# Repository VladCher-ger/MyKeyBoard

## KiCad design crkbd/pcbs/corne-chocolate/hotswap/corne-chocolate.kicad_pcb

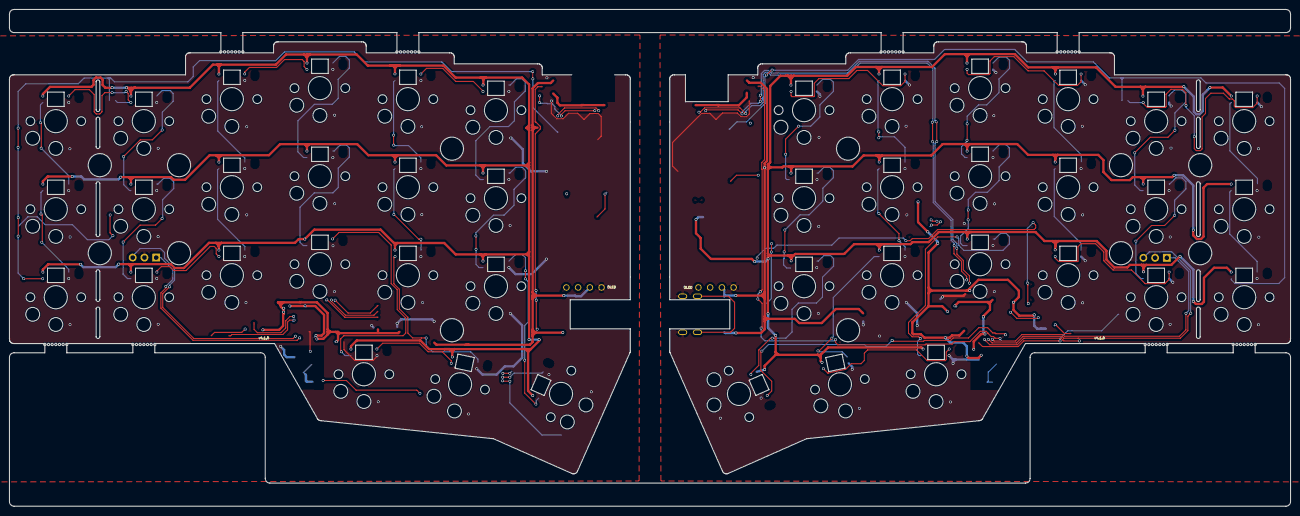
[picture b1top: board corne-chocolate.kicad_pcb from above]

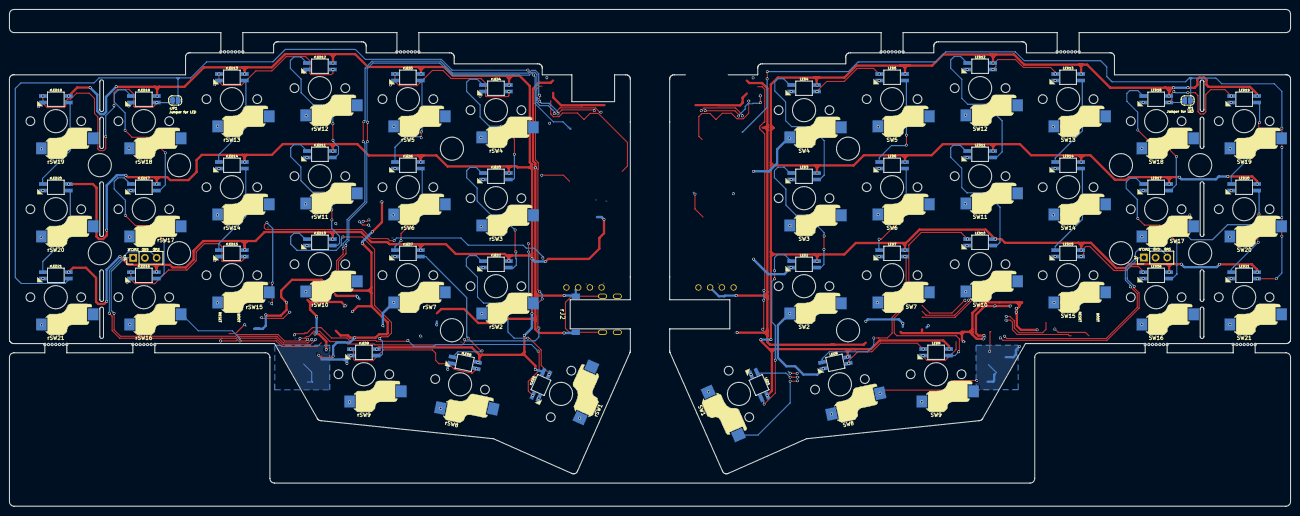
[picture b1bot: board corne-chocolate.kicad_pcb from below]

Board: 2 copper layers, 277.2 x 107.5 mm, 99 parts (89 on the bottom side), 47 nets.

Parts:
BT1, BT2, BT3, BT4: Breakaway Tabs; Breakaway_Tabs
J3: Conn_01x04; OLED
J4: Conn_01x03; PinHeader_1x03_P2.54mm_Vertical
JP1: SolderJumper_2_Bridged; SolderJumper-2_P1.3mm_Open_RoundedPad1.0x1.5mm
LED1, LED2, LED3, LED4, LED5, LED6, LED7, LED8, LED9, LED10, LED11, LED12, LED13, LED14, LED15, LED16, LED17, LED18, LED19, LED20, LED21: YS-SK6812MINI-E
SW1: SW_Push; keyswitch_choc12_hotswap_1.5u
SW2, SW3, SW4, SW5, SW6, SW7, SW8, SW9, SW10, SW11, SW12, SW13, SW14, SW15, SW16, SW17, SW18, SW19, SW20, SW21: SW_Push; keyswitch_choc12_hotswap_1u
rBT1, rBT2, rBT3, rBT4: Breakaway Tabs; Breakaway_Tabs
rJ2: TRS; PJ-398A-5A_PJ-399B-6A
rJ3: Conn_01x04; OLED
rJ4: Conn_01x03; PinHeader_1x03_P2.54mm_Vertical
rJP1: SolderJumper_2_Bridged; SolderJumper-2_P1.3mm_Open_RoundedPad1.0x1.5mm
rLED1, rLED2, rLED3, rLED4, rLED5, rLED6, rLED7, rLED8, rLED9, rLED10, rLED11, rLED12, rLED13, rLED14, rLED15, rLED16, rLED17, rLED18, rLED19, rLED20, rLED21: YS-SK6812MINI-E
rSW1: SW_Push; keyswitch_choc12_hotswap_1.5u
rSW2, rSW3, rSW4, rSW5, rSW6, rSW7, rSW8, rSW9, rSW10, rSW11, rSW12, rSW13, rSW14, rSW15, rSW16, rSW17, rSW18, rSW19, rSW20, rSW21: SW_Push; keyswitch_choc12_hotswap_1u

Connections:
+5VR: rJ2.T, rJ3.3
GND: J3.4, J4.2, LED1.3 (VSS), LED2.3 (VSS), LED3.3 (VSS), LED4.3 (VSS), LED5.3 (VSS), LED6.3 (VSS), LED7.3 (VSS), LED8.3 (VSS), LED9.3 (VSS), LED10.3 (VSS), LED11.3 (VSS), LED12.3 (VSS), LED13.3 (VSS), LED14.3 (VSS), LED15.3 (VSS), LED16.3 (VSS), LED17.3 (VSS), LED18.3 (VSS), LED19.3 (VSS), LED20.3 (VSS), LED21.3 (VSS)
GNDR: rJ2.S, rJ3.4, rJ4.2, rLED1.3 (VSS), rLED2.3 (VSS), rLED3.3 (VSS), rLED4.3 (VSS), rLED5.3 (VSS), rLED6.3 (VSS), rLED7.3 (VSS), rLED8.3 (VSS), rLED9.3 (VSS), rLED10.3 (VSS), rLED11.3 (VSS), rLED12.3 (VSS), rLED13.3 (VSS), rLED14.3 (VSS), rLED15.3 (VSS), rLED16.3 (VSS), rLED17.3 (VSS), rLED18.3 (VSS), rLED19.3 (VSS), rLED20.3 (VSS), rLED21.3 (VSS)
unnamed: JP1.1 (A), LED18.2 (DOUT), LED19.4 (DIN)
unnamed: JP1.2 (B), LED21.2 (DOUT)
unnamed: LED1.2 (DOUT), LED2.4 (DIN)
unnamed: LED1.1 (VDD), LED2.1 (VDD), LED3.1 (VDD), LED4.1 (VDD), LED5.1 (VDD), LED6.1 (VDD), LED7.1 (VDD), LED8.1 (VDD), LED9.1 (VDD), LED10.1 (VDD), LED11.1 (VDD), LED12.1 (VDD), LED13.1 (VDD), LED14.1 (VDD), LED15.1 (VDD), LED16.1 (VDD), LED17.1 (VDD), LED18.1 (VDD), LED19.1 (VDD), LED20.1 (VDD), LED21.1 (VDD)
unnamed: LED2.2 (DOUT), LED3.4 (DIN)
unnamed: LED3.2 (DOUT), LED4.4 (DIN)
unnamed: LED4.2 (DOUT), LED5.4 (DIN)
unnamed: LED5.2 (DOUT), LED6.4 (DIN)
unnamed: LED6.2 (DOUT), LED7.4 (DIN)
unnamed: LED7.2 (DOUT), LED8.4 (DIN)
unnamed: LED8.2 (DOUT), LED9.4 (DIN)
unnamed: LED9.2 (DOUT), LED10.4 (DIN)
unnamed: LED10.2 (DOUT), LED11.4 (DIN)
unnamed: LED11.2 (DOUT), LED12.4 (DIN)
unnamed: LED12.2 (DOUT), LED13.4 (DIN)
unnamed: LED13.2 (DOUT), LED14.4 (DIN)
unnamed: LED14.2 (DOUT), LED15.4 (DIN)
unnamed: LED15.2 (DOUT), LED16.4 (DIN)
unnamed: LED16.2 (DOUT), LED17.4 (DIN)
unnamed: LED17.2 (DOUT), LED18.4 (DIN)
unnamed: LED19.2 (DOUT), LED20.4 (DIN)
unnamed: LED20.2 (DOUT), LED21.4 (DIN)
unnamed: rJP1.1 (A), rLED18.2 (DOUT), rLED19.4 (DIN)
unnamed: rJP1.2 (B), rLED21.2 (DOUT)
unnamed: rLED1.2 (DOUT), rLED2.4 (DIN)
unnamed: rLED1.1 (VDD), rLED2.1 (VDD), rLED3.1 (VDD), rLED4.1 (VDD), rLED5.1 (VDD), rLED6.1 (VDD), rLED7.1 (VDD), rLED8.1 (VDD), rLED9.1 (VDD), rLED10.1 (VDD), rLED11.1 (VDD), rLED12.1 (VDD), rLED13.1 (VDD), rLED14.1 (VDD), rLED15.1 (VDD), rLED16.1 (VDD), rLED17.1 (VDD), rLED18.1 (VDD), rLED19.1 (VDD), rLED20.1 (VDD), rLED21.1 (VDD)
unnamed: rLED2.2 (DOUT), rLED3.4 (DIN)
unnamed: rLED3.2 (DOUT), rLED4.4 (DIN)
unnamed: rLED4.2 (DOUT), rLED5.4 (DIN)
unnamed: rLED5.2 (DOUT), rLED6.4 (DIN)
unnamed: rLED6.2 (DOUT), rLED7.4 (DIN)
unnamed: rLED7.2 (DOUT), rLED8.4 (DIN)
unnamed: rLED8.2 (DOUT), rLED9.4 (DIN)
unnamed: rLED9.2 (DOUT), rLED10.4 (DIN)
unnamed: rLED10.2 (DOUT), rLED11.4 (DIN)
unnamed: rLED11.2 (DOUT), rLED12.4 (DIN)
unnamed: rLED12.2 (DOUT), rLED13.4 (DIN)
unnamed: rLED13.2 (DOUT), rLED14.4 (DIN)
unnamed: rLED14.2 (DOUT), rLED15.4 (DIN)
unnamed: rLED15.2 (DOUT), rLED16.4 (DIN)
unnamed: rLED16.2 (DOUT), rLED17.4 (DIN)
unnamed: rLED17.2 (DOUT), rLED18.4 (DIN)
unnamed: rLED19.2 (DOUT), rLED20.4 (DIN)
unnamed: rLED20.2 (DOUT), rLED21.4 (DIN)

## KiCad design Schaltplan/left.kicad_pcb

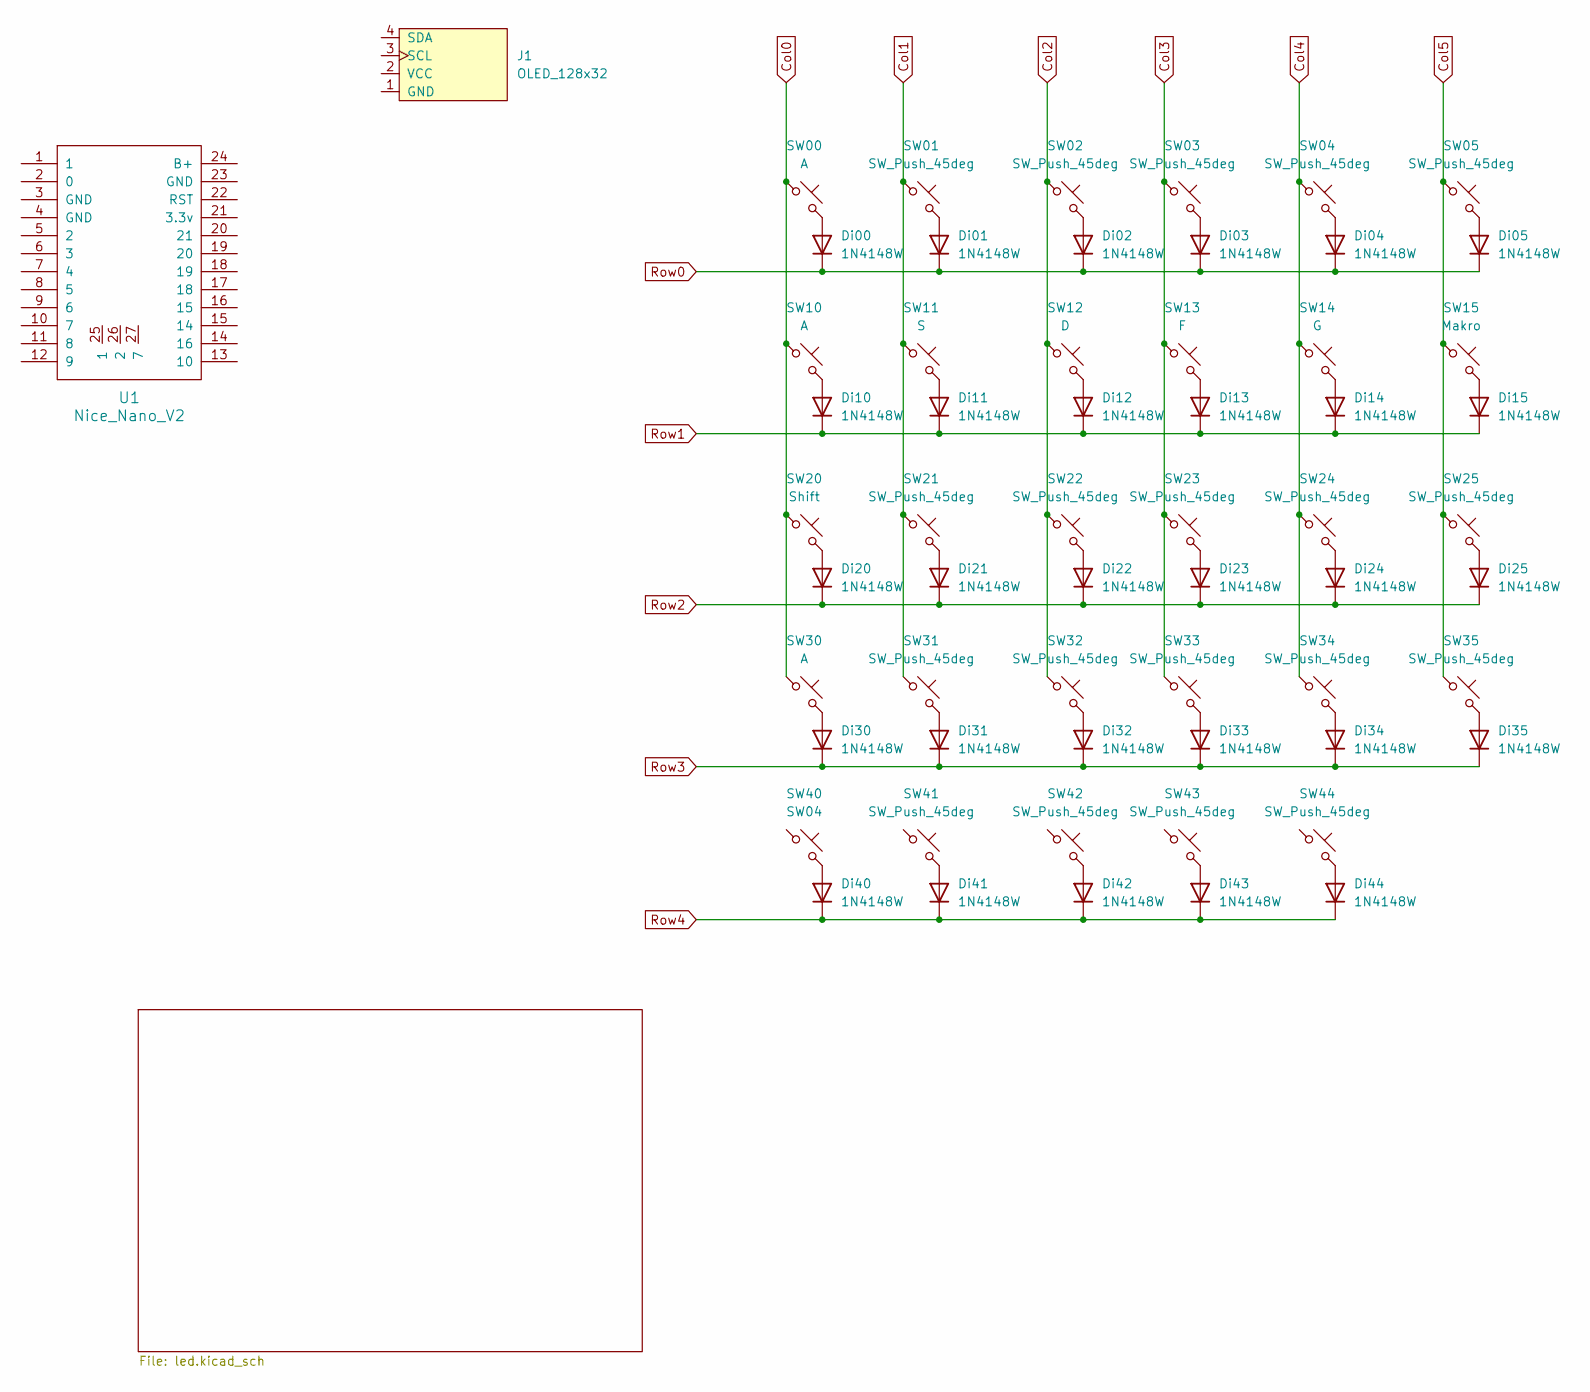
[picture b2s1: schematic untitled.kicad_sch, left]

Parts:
Di00, Di01, Di02, Di03, Di04, Di05, Di10, Di11, Di12, Di13, Di14, Di15, Di20, Di21, Di22, Di23, Di24, Di25, Di30, Di31, Di32, Di33, Di34, Di35, Di40, Di41, Di42, Di43, Di44: 1N4148W; D_SOD-123
J1: OLED_128x32
SW00, SW10, SW30: A; Hotswap_MX_1.00u
SW01, SW02, SW03, SW04, SW05, SW21, SW22, SW23, SW24, SW25, SW31, SW32, SW33, SW34, SW35, SW41, SW43, SW44: SW_Push_45deg; Hotswap_MX_1.00u
SW11: S; Hotswap_MX_1.00u
SW12: D; Hotswap_MX_1.00u
SW13: F; Hotswap_MX_1.00u
SW14: G; Hotswap_MX_1.00u
SW15: Makro; Hotswap_MX_1.00u
SW20: Shift; Hotswap_MX_1.00u
SW40: SW04; Hotswap_MX_1.00u
SW42: SW_Push_45deg; Hotswap_MX_1.75u
U1: Nice_Nano_V2

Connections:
Col0: SW00.1, SW10.1, SW20.1, SW30.1
Col1: SW01.1, SW11.1, SW21.1, SW31.1
Col2: SW02.1, SW12.1, SW22.1, SW32.1
Col3: SW03.1, SW13.1, SW23.1, SW33.1
Col4: SW04.1, SW14.1, SW24.1, SW34.1
Col5: SW05.1, SW15.1, SW25.1, SW35.1
unnamed: Di00.2 (A), SW00.2
unnamed: Di01.2 (A), SW01.2
unnamed: Di02.2 (A), SW02.2
unnamed: Di03.2 (A), SW03.2
unnamed: Di04.2 (A), SW04.2
unnamed: Di05.2 (A), SW05.2
unnamed: Di10.2 (A), SW10.2
unnamed: Di11.2 (A), SW11.2
unnamed: Di12.2 (A), SW12.2
unnamed: Di13.2 (A), SW13.2
unnamed: Di14.2 (A), SW14.2
unnamed: Di15.2 (A), SW15.2
unnamed: Di20.2 (A), SW20.2
unnamed: Di21.2 (A), SW21.2
unnamed: Di22.2 (A), SW22.2
unnamed: Di23.2 (A), SW23.2
unnamed: Di24.2 (A), SW24.2
unnamed: Di25.2 (A), SW25.2
unnamed: Di30.2 (A), SW30.2
unnamed: Di31.2 (A), SW31.2
unnamed: Di32.2 (A), SW32.2
unnamed: Di33.2 (A), SW33.2
unnamed: Di34.2 (A), SW34.2
unnamed: Di35.2 (A), SW35.2
unnamed: Di40.2 (A), SW40.2
unnamed: Di41.2 (A), SW41.2
unnamed: Di42.2 (A), SW42.2
unnamed: Di43.2 (A), SW43.2
unnamed: Di44.2 (A), SW44.2
Row0: Di00.1 (K), Di01.1 (K), Di02.1 (K), Di03.1 (K), Di04.1 (K), Di05.1 (K)
Row1: Di10.1 (K), Di11.1 (K), Di12.1 (K), Di13.1 (K), Di14.1 (K), Di15.1 (K)
Row2: Di20.1 (K), Di21.1 (K), Di22.1 (K), Di23.1 (K), Di24.1 (K), Di25.1 (K)
Row3: Di30.1 (K), Di31.1 (K), Di32.1 (K), Di33.1 (K), Di34.1 (K), Di35.1 (K)
Row4: Di40.1 (K), Di41.1 (K), Di42.1 (K), Di43.1 (K), Di44.1 (K)

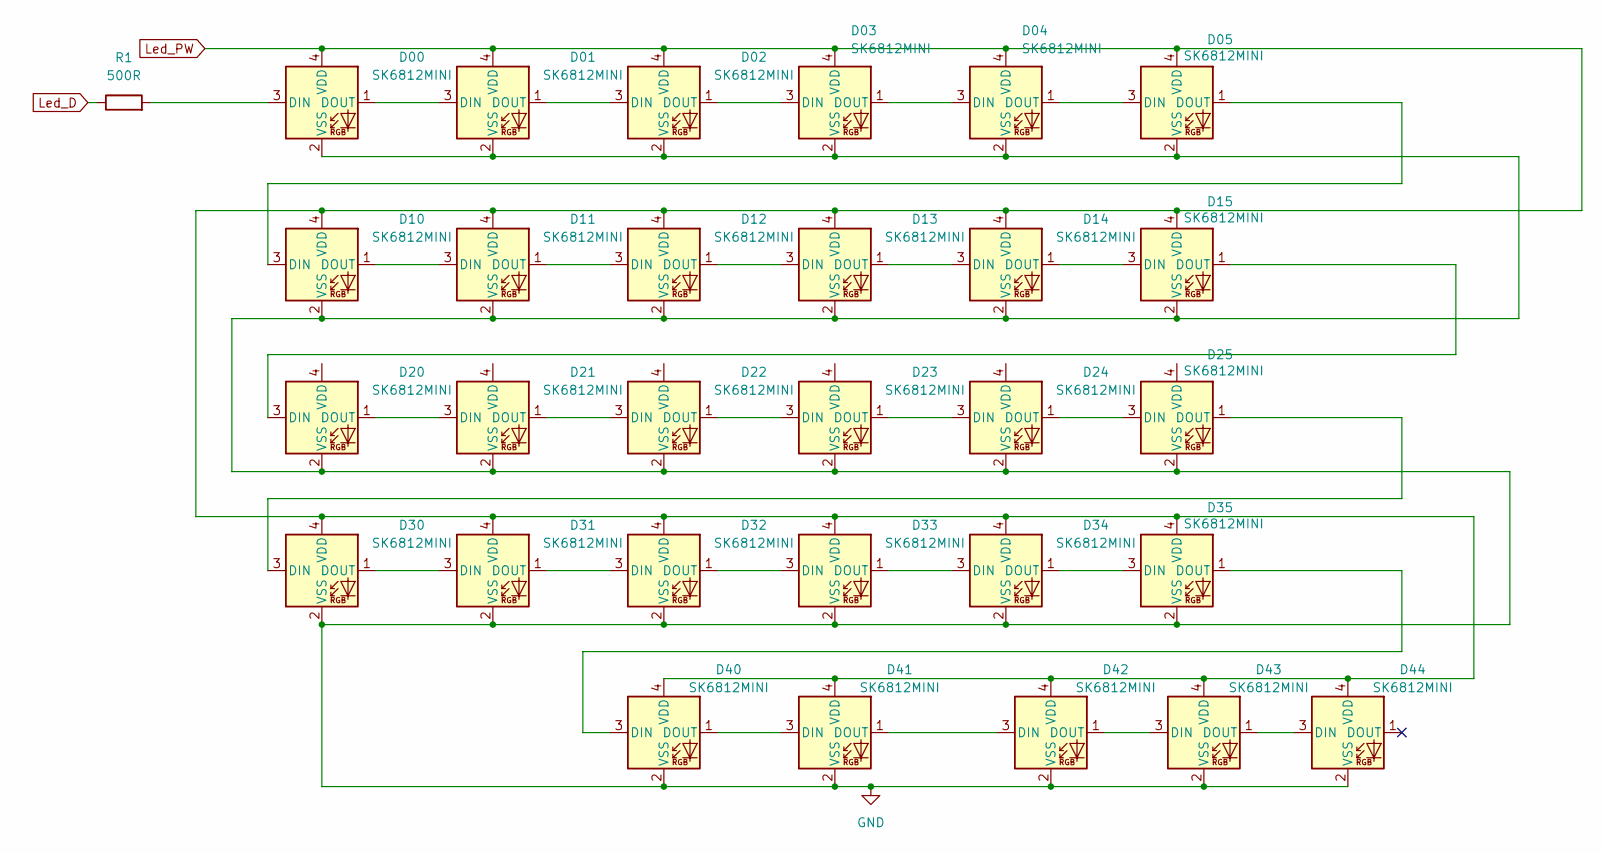
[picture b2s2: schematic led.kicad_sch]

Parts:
D00, D01, D02, D03, D04, D05, D10, D11, D12, D13, D14, D15, D20, D21, D22, D23, D24, D25, D30, D31, D32, D33, D34, D35, D40, D41, D42, D43, D44: SK6812MINI; SK6812-MINI-E
R1: 500R; R_Axial_DIN0414_L11.9mm_D4.5mm_P15.24mm_Horizontal

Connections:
GND: D00.2 (VSS), D01.2 (VSS), D02.2 (VSS), D03.2 (VSS), D04.2 (VSS), D05.2 (VSS), D10.2 (VSS), D11.2 (VSS), D12.2 (VSS), D13.2 (VSS), D14.2 (VSS), D15.2 (VSS), D20.2 (VSS), D21.2 (VSS), D22.2 (VSS), D23.2 (VSS), D24.2 (VSS), D25.2 (VSS), D30.2 (VSS), D31.2 (VSS), D32.2 (VSS), D33.2 (VSS), D34.2 (VSS), D35.2 (VSS), D40.2 (VSS), D41.2 (VSS), D42.2 (VSS), D43.2 (VSS), D44.2 (VSS)
Led_D: R1.1
Led_PW: D00.4 (VDD), D01.4 (VDD), D02.4 (VDD), D03.4 (VDD), D04.4 (VDD), D05.4 (VDD), D10.4 (VDD), D11.4 (VDD), D12.4 (VDD), D13.4 (VDD), D14.4 (VDD), D15.4 (VDD), D30.4 (VDD), D31.4 (VDD), D32.4 (VDD), D33.4 (VDD), D34.4 (VDD), D35.4 (VDD), D40.4 (VDD), D41.4 (VDD), D42.4 (VDD), D43.4 (VDD), D44.4 (VDD)
unnamed: D00.3 (DIN), R1.2
unnamed: D00.1 (DOUT), D01.3 (DIN)
unnamed: D01.1 (DOUT), D02.3 (DIN)
unnamed: D02.1 (DOUT), D03.3 (DIN)
unnamed: D03.1 (DOUT), D04.3 (DIN)
unnamed: D04.1 (DOUT), D05.3 (DIN)
unnamed: D05.1 (DOUT), D10.3 (DIN)
unnamed: D10.1 (DOUT), D11.3 (DIN)
unnamed: D11.1 (DOUT), D12.3 (DIN)
unnamed: D12.1 (DOUT), D13.3 (DIN)
unnamed: D13.1 (DOUT), D14.3 (DIN)
unnamed: D14.1 (DOUT), D15.3 (DIN)
unnamed: D15.1 (DOUT), D20.3 (DIN)
unnamed: D20.1 (DOUT), D21.3 (DIN)
unnamed: D21.1 (DOUT), D22.3 (DIN)
unnamed: D22.1 (DOUT), D23.3 (DIN)
unnamed: D23.1 (DOUT), D24.3 (DIN)
unnamed: D24.1 (DOUT), D25.3 (DIN)
unnamed: D25.1 (DOUT), D30.3 (DIN)
unnamed: D30.1 (DOUT), D31.3 (DIN)
unnamed: D31.1 (DOUT), D32.3 (DIN)
unnamed: D32.1 (DOUT), D33.3 (DIN)
unnamed: D33.1 (DOUT), D34.3 (DIN)
unnamed: D34.1 (DOUT), D35.3 (DIN)
unnamed: D35.1 (DOUT), D40.3 (DIN)
unnamed: D40.1 (DOUT), D41.3 (DIN)
unnamed: D41.1 (DOUT), D42.3 (DIN)
unnamed: D42.1 (DOUT), D43.3 (DIN)
unnamed: D43.1 (DOUT), D44.3 (DIN)

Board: 2 copper layers, 90 parts (60 on the bottom side), 71 nets, no tracks yet.

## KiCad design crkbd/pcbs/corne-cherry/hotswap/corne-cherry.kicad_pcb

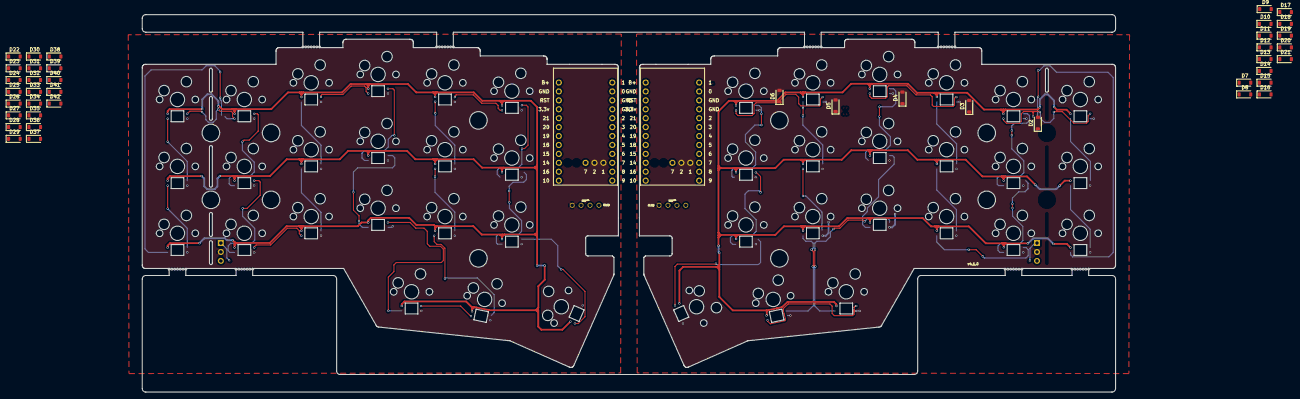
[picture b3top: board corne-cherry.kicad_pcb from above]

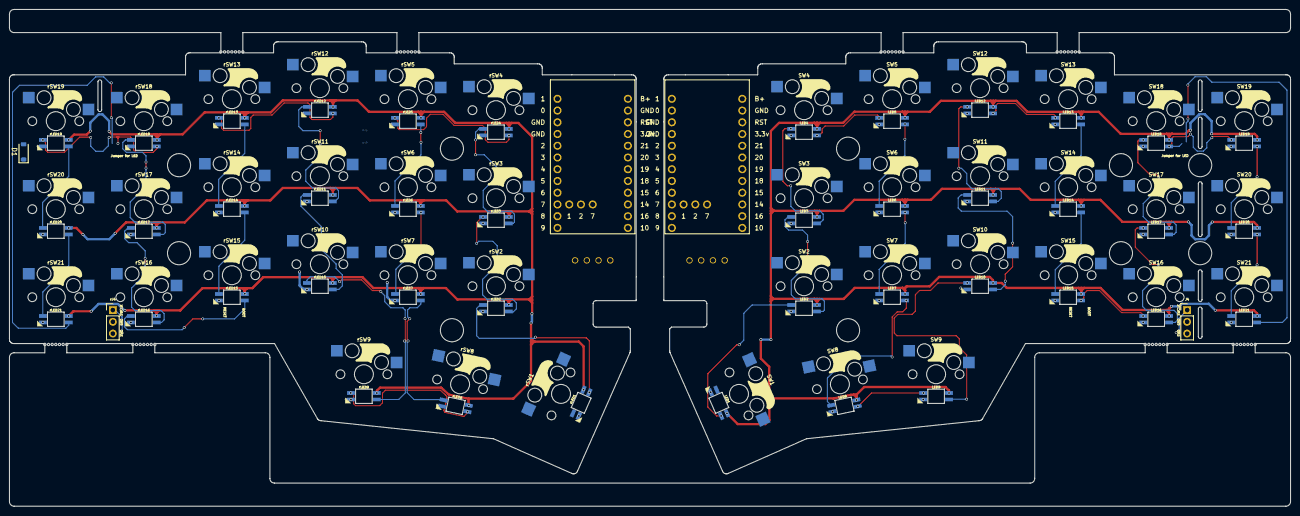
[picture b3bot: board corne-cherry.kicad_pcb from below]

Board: 2 copper layers, 277.2 x 107.5 mm, 140 parts (89 on the bottom side), 100 nets.

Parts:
BT1, BT2, BT3, BT4: Breakaway Tabs; Breakaway_Tabs
D1, D2, D3, D4, D5, D6, D7, D8, D9, D10, D11, D12, D13, D14, D15, D16, D17, D18, D19, D20, D21, D22, D23, D24, D25, D26, D27, D28, D29, D30, D31, D32, D33, D34, D35, D36, D37, D38, D39, D40, D41, D42: Diode; D_SOD-123
J3: Conn_01x04; OLED
J4: Conn_01x03; PinHeader_1x03_P2.54mm_Vertical
LED1, LED2, LED3, LED4, LED5, LED6, LED7, LED8, LED9, LED10, LED11, LED12, LED13, LED14, LED15, LED16, LED17, LED18, LED19, LED20, LED21: YS-SK6812MINI-E
SW1: SW_Push; keyswitch_cherrymx_hotswap_1.5u
SW2, SW3, SW4, SW5, SW6, SW7, SW8, SW9, SW10, SW11, SW12, SW13, SW14, SW15, SW16, SW17, SW18, SW19, SW20, SW21: SW_Push; keyswitch_cherrymx_hotswap_1u
U1, U2: Nice_Nano_V2
rBT1, rBT2, rBT3, rBT4: Breakaway Tabs; Breakaway_Tabs
rJ3: Conn_01x04; OLED
rJ4: Conn_01x03; PinHeader_1x03_P2.54mm_Vertical
rLED1, rLED2, rLED3, rLED4, rLED5, rLED6, rLED7, rLED8, rLED9, rLED10, rLED11, rLED12, rLED13, rLED14, rLED15, rLED16, rLED17, rLED18, rLED19, rLED20, rLED21: YS-SK6812MINI-E
rSW1: SW_Push; keyswitch_cherrymx_hotswap_1.5u
rSW2, rSW3, rSW4, rSW5, rSW6, rSW7, rSW8, rSW9, rSW10, rSW11, rSW12, rSW13, rSW14, rSW15, rSW16, rSW17, rSW18, rSW19, rSW20, rSW21: SW_Push; keyswitch_cherrymx_hotswap_1u

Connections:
C0: rSW19.1, rSW20.1, rSW21.1
C1: rSW16.1, rSW17.1, rSW18.1
C2: rSW13.1, rSW14.1, rSW15.1
C3: rSW9.1, rSW10.1, rSW11.1, rSW12.1
C4: rSW5.1, rSW6.1, rSW7.1, rSW8.1
C5: rSW1.1, rSW2.1, rSW3.1, rSW4.1
CL0: SW19.1, SW20.1, SW21.1
CL1: SW16.1, SW17.1, SW18.1
CL2: SW13.1, SW14.1, SW15.1
CL3: SW9.1, SW10.1, SW11.1, SW12.1
CL4: SW5.1, SW6.1, SW7.1, SW8.1
CL5: SW1.1, SW2.1, SW3.1, SW4.1
GND: J3.4, J4.2, LED1.3 (VSS), LED2.3 (VSS), LED3.3 (VSS), LED4.3 (VSS), LED5.3 (VSS), LED6.3 (VSS), LED7.3 (VSS), LED8.3 (VSS), LED9.3 (VSS), LED10.3 (VSS), LED11.3 (VSS), LED12.3 (VSS), LED13.3 (VSS), LED14.3 (VSS), LED15.3 (VSS), LED16.3 (VSS), LED17.3 (VSS), LED18.3 (VSS), LED19.3 (VSS), LED20.3 (VSS), LED21.3 (VSS)
GNDR: U1.3 (GND), U1.4 (GND), U1.23 (GND), rJ3.4, rJ4.2, rLED1.3 (VSS), rLED2.3 (VSS), rLED3.3 (VSS), rLED4.3 (VSS), rLED5.3 (VSS), rLED6.3 (VSS), rLED7.3 (VSS), rLED8.3 (VSS), rLED9.3 (VSS), rLED10.3 (VSS), rLED11.3 (VSS), rLED12.3 (VSS), rLED13.3 (VSS), rLED14.3 (VSS), rLED15.3 (VSS), rLED16.3 (VSS), rLED17.3 (VSS), rLED18.3 (VSS), rLED19.3 (VSS), rLED20.3 (VSS), rLED21.3 (VSS)
unnamed: D1.2 (A), rSW19.2
unnamed: D2.2 (A), rSW18.2
unnamed: D3.2 (A), rSW13.2
unnamed: D4.2 (A), rSW12.2
unnamed: D5.2 (A), rSW5.2
unnamed: D6.2 (A), rSW4.2
unnamed: D7.2 (A), rSW20.2
unnamed: D8.2 (A), rSW17.2
unnamed: D9.2 (A), rSW14.2
unnamed: D10.2 (A), rSW11.2
unnamed: D11.2 (A), rSW6.2
unnamed: D12.2 (A), rSW3.2
unnamed: D19.2 (A), rSW9.2
unnamed: D20.2 (A), rSW8.2
unnamed: D21.2 (A), rSW1.2
unnamed: D22.2 (A), SW19.2
unnamed: D23.2 (A), SW18.2
unnamed: D24.2 (A), SW13.2
unnamed: D25.2 (A), SW12.2
unnamed: D26.2 (A), SW5.2
unnamed: D27.2 (A), SW4.2
unnamed: D28.2 (A), SW20.2
unnamed: D29.2 (A), SW17.2
unnamed: D30.2 (A), SW14.2
unnamed: D31.2 (A), SW11.2
unnamed: D32.2 (A), SW6.2
unnamed: D33.2 (A), SW3.2
unnamed: D34.2 (A), SW21.2
unnamed: D35.2 (A), SW16.2
unnamed: D36.2 (A), SW15.2
unnamed: D37.2 (A), SW10.2
unnamed: D38.2 (A), SW7.2
unnamed: D39.2 (A), SW2.2
unnamed: D40.2 (A), SW9.2
unnamed: D41.2 (A), SW8.2
unnamed: D42.2 (A), SW1.2
unnamed: LED1.2 (DOUT), LED2.4 (DIN)
unnamed: LED1.1 (VDD), LED2.1 (VDD), LED3.1 (VDD), LED4.1 (VDD), LED5.1 (VDD), LED6.1 (VDD), LED7.1 (VDD), LED8.1 (VDD), LED9.1 (VDD), LED10.1 (VDD), LED11.1 (VDD), LED12.1 (VDD), LED13.1 (VDD), LED14.1 (VDD), LED15.1 (VDD), LED16.1 (VDD), LED17.1 (VDD), LED18.1 (VDD), LED19.1 (VDD), LED20.1 (VDD), LED21.1 (VDD)
unnamed: LED2.2 (DOUT), LED3.4 (DIN)
unnamed: LED3.2 (DOUT), LED4.4 (DIN)
unnamed: LED4.2 (DOUT), LED5.4 (DIN)
unnamed: LED5.2 (DOUT), LED6.4 (DIN)
unnamed: LED6.2 (DOUT), LED7.4 (DIN)
unnamed: LED7.2 (DOUT), LED8.4 (DIN)
unnamed: LED8.2 (DOUT), LED9.4 (DIN)
unnamed: LED9.2 (DOUT), LED10.4 (DIN)
unnamed: LED10.2 (DOUT), LED11.4 (DIN)
unnamed: LED11.2 (DOUT), LED12.4 (DIN)
unnamed: LED12.2 (DOUT), LED13.4 (DIN)
unnamed: LED13.2 (DOUT), LED14.4 (DIN)
unnamed: LED14.2 (DOUT), LED15.4 (DIN)
unnamed: LED15.2 (DOUT), LED16.4 (DIN)
unnamed: LED16.2 (DOUT), LED17.4 (DIN)
unnamed: LED17.2 (DOUT), LED18.4 (DIN)
unnamed: LED18.2 (DOUT), LED19.4 (DIN)
unnamed: LED19.2 (DOUT), LED20.4 (DIN)
unnamed: LED20.2 (DOUT), LED21.4 (DIN)
unnamed: rLED1.2 (DOUT), rLED2.4 (DIN)
unnamed: rLED1.1 (VDD), rLED2.1 (VDD), rLED3.1 (VDD), rLED4.1 (VDD), rLED5.1 (VDD), rLED6.1 (VDD), rLED7.1 (VDD), rLED8.1 (VDD), rLED9.1 (VDD), rLED10.1 (VDD), rLED11.1 (VDD), rLED12.1 (VDD), rLED13.1 (VDD), rLED14.1 (VDD), rLED15.1 (VDD), rLED16.1 (VDD), rLED17.1 (VDD), rLED18.1 (VDD), rLED19.1 (VDD), rLED20.1 (VDD), rLED21.1 (VDD)
unnamed: rLED2.2 (DOUT), rLED3.4 (DIN)
unnamed: rLED3.2 (DOUT), rLED4.4 (DIN)
unnamed: rLED4.2 (DOUT), rLED5.4 (DIN)
unnamed: rLED5.2 (DOUT), rLED6.4 (DIN)
unnamed: rLED6.2 (DOUT), rLED7.4 (DIN)
unnamed: rLED7.2 (DOUT), rLED8.4 (DIN)
unnamed: rLED8.2 (DOUT), rLED9.4 (DIN)
unnamed: rLED9.2 (DOUT), rLED10.4 (DIN)
unnamed: rLED10.2 (DOUT), rLED11.4 (DIN)
unnamed: rLED11.2 (DOUT), rLED12.4 (DIN)
unnamed: rLED12.2 (DOUT), rLED13.4 (DIN)
unnamed: rLED13.2 (DOUT), rLED14.4 (DIN)
unnamed: rLED14.2 (DOUT), rLED15.4 (DIN)
unnamed: rLED15.2 (DOUT), rLED16.4 (DIN)
unnamed: rLED16.2 (DOUT), rLED17.4 (DIN)
unnamed: rLED17.2 (DOUT), rLED18.4 (DIN)
unnamed: rLED18.2 (DOUT), rLED19.4 (DIN)
unnamed: rLED19.2 (DOUT), rLED20.4 (DIN)
unnamed: rLED20.2 (DOUT), rLED21.4 (DIN)
R0: D1.1 (K), D2.1 (K), D3.1 (K), D4.1 (K), D5.1 (K), D6.1 (K)
R1: D7.1 (K), D8.1 (K), D9.1 (K), D10.1 (K), D11.1 (K), D12.1 (K)
R2: D13.1 (K), D14.1 (K), D15.1 (K), D16.1 (K), D17.1 (K), D18.1 (K)
R3: D19.1 (K), D20.1 (K), D21.1 (K)
RL0: D22.1 (K), D23.1 (K), D24.1 (K), D25.1 (K), D26.1 (K), D27.1 (K)
RL1: D28.1 (K), D29.1 (K), D30.1 (K), D31.1 (K), D32.1 (K), D33.1 (K)
RL2: D34.1 (K), D35.1 (K), D36.1 (K), D37.1 (K), D38.1 (K), D39.1 (K)
RL3: D40.1 (K), D41.1 (K), D42.1 (K)

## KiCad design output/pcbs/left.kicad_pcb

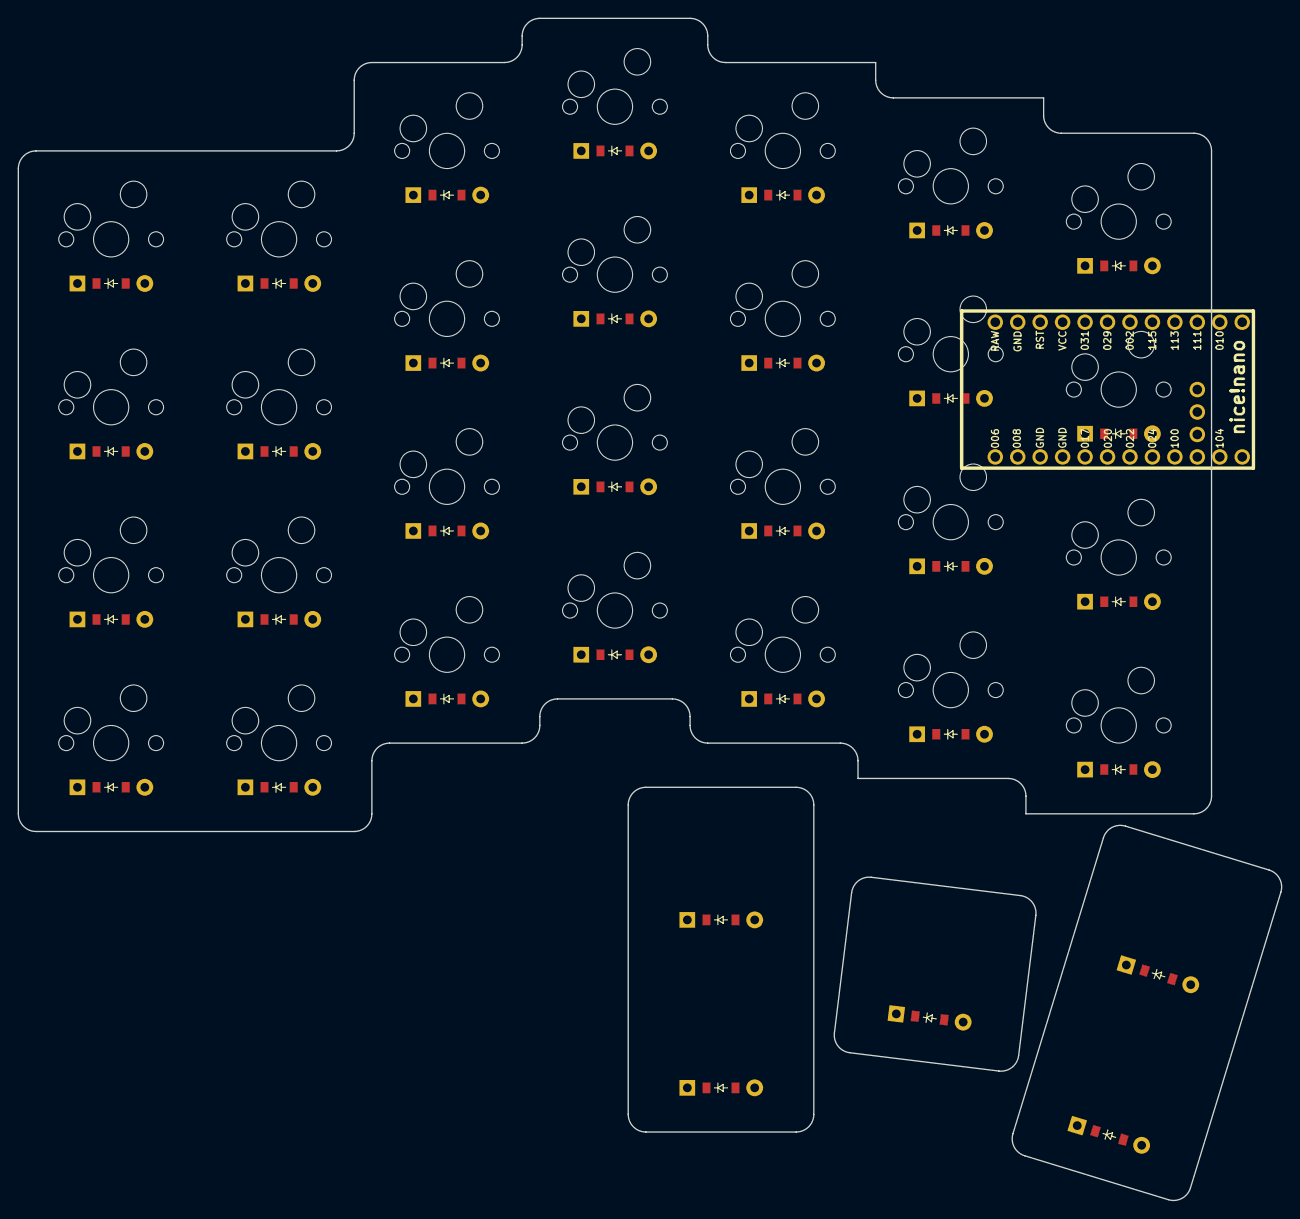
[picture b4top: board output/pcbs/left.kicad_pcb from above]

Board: 2 copper layers, 142.9 x 133.7 mm, 62 parts (0 on the bottom side), 36 nets, no tracks yet.

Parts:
D1, D2, D3, D4, D5, D6, D7, D8, D9, D10, D11, D12, D13, D14, D15, D16, D17, D18, D19, D20, D21, D22, D23, D24, D25, D26, D27, D28, D29, D30, D31, D32, D33: ComboDiode
MCU1: nice_nano
S1, S2, S3, S4, S5, S6, S7, S8, S9, S10, S11, S12, S13, S14, S15, S16, S17, S18, S19, S20, S21, S22, S23, S24, S25, S26, S27, S28: MX

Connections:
GND: MCU1.3, MCU1.4, MCU1.23
P006: MCU1.1, S1.1, S2.1, S3.1, S4.1
P017: MCU1.5, S5.1, S6.1, S7.1, S8.1
P020: MCU1.6, S9.1, S10.1, S11.1, S12.1
P022: MCU1.7, S13.1, S14.1, S15.1, S16.1
P024: MCU1.8, S17.1, S18.1, S19.1, S20.1
P100: MCU1.9, S21.1, S22.1, S23.1, S24.1
P104: MCU1.11, S25.1, S26.1, S27.1, S28.1
index_bottom: D17.2, S17.2
index_home: D18.2, S18.2
index_number: D20.2, S20.2
index_top: D19.2, S19.2
inner_bottom: D21.2, S21.2
inner_home: D22.2, S22.2
inner_number: D24.2, S24.2
inner_top: D23.2, S23.2
makros_bottom: D25.2, S25.2
makros_home: D26.2, S26.2
makros_number: D28.2, S28.2
makros_top: D27.2, S27.2
middle_bottom: D13.2, S13.2
middle_home: D14.2, S14.2
middle_number: D16.2, S16.2
middle_top: D15.2, S15.2
outer_bottom: D1.2, S1.2
outer_home: D2.2, S2.2
outer_number: D4.2, S4.2
outer_top: D3.2, S3.2
pinky_bottom: D5.2, S5.2
pinky_home: D6.2, S6.2
pinky_number: D8.2, S8.2
pinky_top: D7.2, S7.2
ring_bottom: D9.2, S9.2
ring_home: D10.2, S10.2
ring_number: D12.2, S12.2
ring_top: D11.2, S11.2

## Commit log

2025-06-10 ergogen
2025-06-10 scretch
2025-06-11 Left almost ready
2025-06-12 custom crbd
2025-07-01 leds
2025-07-06 underglow test
